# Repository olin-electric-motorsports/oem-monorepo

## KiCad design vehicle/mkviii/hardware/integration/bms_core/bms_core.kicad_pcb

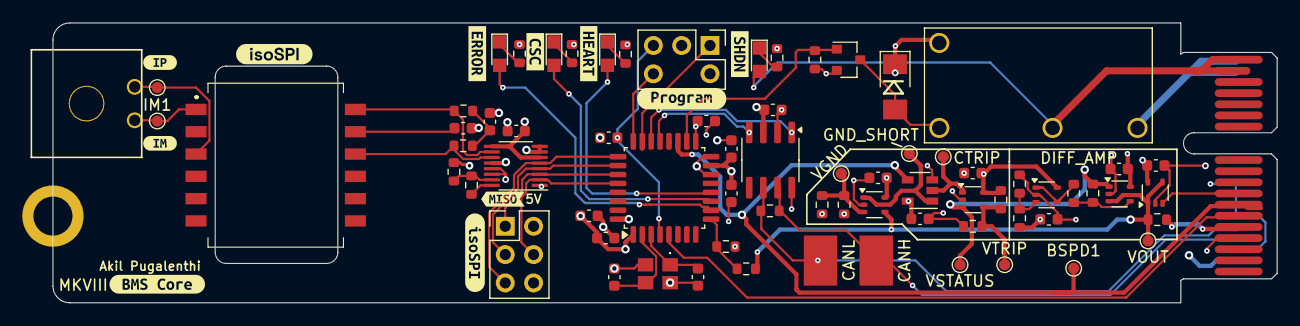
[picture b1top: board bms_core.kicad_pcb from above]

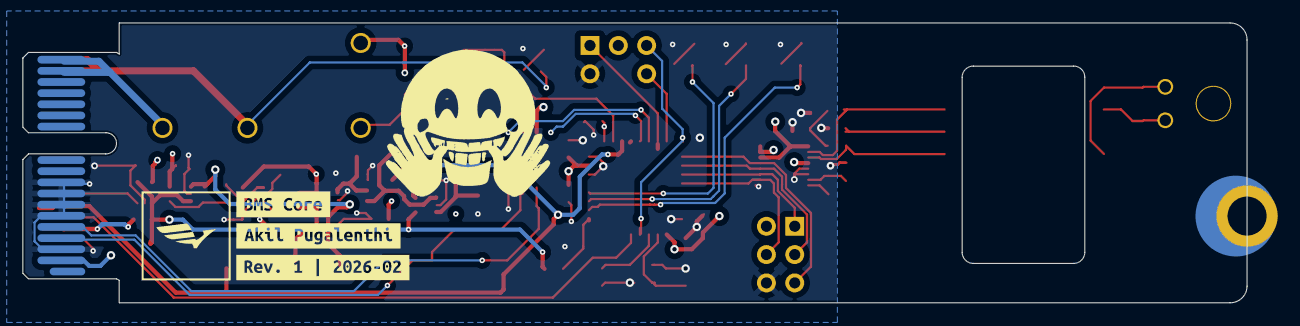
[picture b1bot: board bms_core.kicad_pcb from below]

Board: 4 copper layers, 109.8 x 25.1 mm, 87 parts (3 on the bottom side), 48 nets.

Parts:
BSPD1: BSPD_CURRENT_THRESH; TestPoint_Pad_D1.0mm
C1, C16, C17, C21, C22: C_0.1uF_16V; C_0603_1608Metric
C6, C9, C10, C11, C12, C13: C_0.1uF; C_0603
C7, C8: C_10nF; C_0603
C14, C15: C_30pF_50V; C_0603_1608Metric
C18: C_4.7uF_25V; C_0603_1608Metric
C19: C_10nF_50V; C_0603_1608Metric
C20: C_1uF_25V; C_0603_1608Metric
CANH: CANH1; TP_Hook_SMD
CANL: CANL1; TP_Hook_SMD
D1: LED_AMBER; CHIPLED_0805
D2: LED_GREEN; CHIPLED_0805
D3: LED_RED; CHIPLED_0805
D5: D_Zener_18V_SMBJ5355B-TP; DO-214AA
D6: LED_BLUE; CHIPLED_0805
GND_SHORT: GND_SHORT; TestPoint_Pad_D1.0mm
H2: CONN_MountingHole; PCIe_Mount
IM1: TP_1mm; TestPoint_Pad_D1.0mm
IP1: TP_1mm; TestPoint_Pad_D1.0mm
J1: isoSPI Header; PinHeader_2x03_P2.54mm_Vertical
J3: MicroFit_RA_2
J4: J_Programming_Pin_Header; J_Programming_Pin_Header_Keyed
J5: J_PCIe_x1; J_PCIe_x1_Key
K1: Relay_G5Q-1A4-DC5; Relay_SPST_OMRON-G5Q-1A4_OEM
Q1: SSM3K333R; SOT-23F
R1, R3, R21, R23: 1KR; R_0603
R2: R_5.1k; R_0603_1608Metric
R4: R_10k; R_0603_1608Metric
R5: R_120; R_0603_1608Metric
R7, R12, R15, R16, R19, R24, R25: R_10K; R_0603
R8, R9, R18: R_1K; R_0603
R10, R11: R_60.4; R_0603
R17: R_1M; R_0603
R20: R_576; R_0603
T1: HM2112ZNLT
TP4: CURRENT_TRIP; TestPoint_Pad_D1.0mm
U1, U4, U5, U6, U8: MCP6001; SOT-353_SC-70-5
U3: LTC6820HMS; MSOP-16_3x4mm_P0.5mm
U7: SN74LVC1G32DBVR; SOT-23-5_OEM
U10: STM32G441KBT6; LQFP-32_7x7mm_P0.8mm
U11: MCP2561-E_SN; SOIC-8_3.9x4.9mm_P1.27mm
VGND: V_GND_THRESHOLD; TestPoint_Pad_D1.0mm
VOUT: VOUT; TestPoint_Pad_D1.0mm
VSTATUS: VSTATUS; TestPoint_Pad_D1.0mm
VTRIP: VTRIP; TestPoint_Pad_D1.0mm
Y3: X_16MHz_18pF; FA238160000MBC0 (X_16MHz_18pF_SMD - FA-238_16.0000MB-C0)
kibuzzard-63B930AD: G***; kibuzzard-63B930AD
kibuzzard-63B9305B: G***; kibuzzard-63B9305B
kibuzzard-63B93076: G***; kibuzzard-63B93076
kibuzzard-63BB8A3F: G***; kibuzzard-63BB8A3F
kibuzzard-63BB8A53: G***; kibuzzard-63BB8A53
kibuzzard-63BF4A21: G***; kibuzzard-63BF4A21
kibuzzard-63BF57C4: G***; kibuzzard-63BF57C4
kibuzzard-673AE5D1: G***; kibuzzard-673AE5D1
kibuzzard-673AE69E: G***; kibuzzard-673AE69E
kibuzzard-673AE677: G***; kibuzzard-673AE677
kibuzzard-673AE688: G***; kibuzzard-673AE688
kibuzzard-698026CF: G***; kibuzzard-698026CF
kibuzzard-69802617: G***; kibuzzard-69802617
kibuzzard-69802858: G***; kibuzzard-69802858

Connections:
+3V3: C16.1, C17.1, C18.1, C19.1, C20.1, J4.3, J5.A2 (3.3V), U10.1 (VDD), U10.15 (VDDA), U10.17 (VDD)
+5V: C1.2, C6.1, C9.1, C10.1, C11.1, C12.1, C13.1, C22.1, D5.1 (K), J1.2, J5.B5 (5V), K1.5, R12.2, R17.1, R19.2, R24.1, U1.5 (V+), U3.6 (VDDS), U3.7 (POL), U3.8 (PHA), U3.9 (VDD), U3.12 (MSTR), U4.5 (V+), U5.5 (V+), U6.5 (V+), U7.5 (VCC), U8.5 (V+), U11.3 (VDD)
/BMS_RELAY_DRIVE: Q1.1 (G), R7.2, U10.18 ((TIM4_ETR/USART1_CK/GPIO_EXTI8)PA8)
/BSPD Current Sensor Trigger/CURRENT_TRIP: TP4.1, U6.1, U7.2 (in)
/BSPD Current Sensor Trigger/GND_SHORT: GND_SHORT.1, U5.1, U7.1 (in)
/BSPD Current Sensor Trigger/VSTATUS: R15.2, U4.1, U6.3 (+), VSTATUS.1
/BSPD Current Sensor Trigger/VTRIP: R19.1, R20.1, U6.4 (-), VTRIP.1
/BSPD Current Sensor Trigger/V_GND_THRESHOLD: R17.2, R18.1, U5.3 (+), VGND.1
/BSPD_CURRENT_THRESH: BSPD1.1, J5.B7 (io_3), U7.4 (out), U10.19 ((TIM2_CH3/TIM15_BKIN/USART1_TX/GPIO_EXT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)
/CANH: CANH.1, J5.A4 (CAN+), R5.1, U11.7 (CANH)
/CANL: CANL.1, J5.A5 (CAN-), R5.2, U11.6 (CANL)
/CAN_RX: U10.21 ((FDCAN1_RX/GPIO_EXTI11)PA11), U11.4 (RXD)
/CAN_TX: U10.22 ((FDCAN1_TX/GPIO_EXTI12)PA12), U11.1 (TXD)
/CSC_Comms: D2.2 (A), U10.11 ((TIM3_CH1/TIM16_CH1/GPIO_EXTI6/ADC2_IN3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)
/Error: D3.2 (A), U10.10 ((TIM2_ETR/TIM2_CH1/GPIO_EXTI5/ADC2_IN13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)
/FAN_PWM: J5.B6 (io_1), U10.5 ((TIM2_ETR/TIM2_CH1/GPIO_EXTI0/ADC2_IN1/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)
/Heartbeat: D1.2 (A), U10.12 ((TIM3_CH2/TIM17_CH1/GPIO_EXTI7/ADC2_IN4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)
/IM: IM1.1, J3.1, T1.1
/IP: IP1.1, J3.2, T1.3
/ISO_CS: J1.5, U3.5 (~CS), U10.25 ((TIM2_ETR/TIM2_CH1/GPIO_EXTI15)PA15)
/ISO_MISO: J1.1, U3.3 (MISO), U10.27 ((TIM17_BKIN/SPI1_MISO/TIM3_CH1/TIM16_CH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)
/ISO_MOSI: J1.4, U3.2 (MOSI), U10.28 ((TIM17_CH1/SPI1_MOSI/TIM3_CH2/TIM16_BKI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)
/ISO_SCK: J1.3, U3.4 (SCK), U10.26 ((TIM3_ETR/SPI1_SCK/TIM4_ETR/TIM2_CH2/GP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)
/NRST: C21.1, J4.4, U10.4 ((GPIO_EXTI10)PG10-NRST)
/SHDN_IN: J5.A17 (SHDN_IN/io_22), J5.A18 (SHDN_IN/io_24), K1.3
/SHDN_OUT: D6.2 (A), J5.B17 (SHDN_OUT/io_23), J5.B18 (SHDN_OUT/io_25), K1.2
/SWCLK: J4.5, U10.24 ((SYS_JTCK-SWCLK/GPIO_EXTI14)PA14)
/SWDIO: J4.1, U10.23 ((SYS_JTMS-SWDIO/GPIO_EXTI13)PA13)
/VOUT_CURRENT_SENSE: R2.1, R12.1, U1.1, U1.4 (-), U4.3 (+), U5.4 (-), VOUT.1
GND: C1.1, C6.2, C7.2, C8.2, C9.2, C10.2, C11.2, C12.2, C13.2, C14.2, C15.2, C16.2, C17.2, C18.2, C19.2, C20.2, C21.2, C22.2, J1.6, J4.2, J5.A3 (GND), J5.A6 (io_0), J5.A7 (io_2), J5.A8 (io_4), J5.A9 (io_6), J5.B4 (GND), Q1.2 (S), R1.2, R3.2, R4.2, R7.1, R9.2, R18.2, R20.2, R21.2, R23.2, R25.2, U1.2 (V-), U3.1 (EN), U3.13 (SLOW), U3.14 (GND), U4.2 (V-), U5.2 (V-), U6.2 (V-), U7.3 (GND), U8.2 (V-), U10.14 (VSSA), U10.16 (VSS), U10.32 (VSS), U11.2 (VSS), U11.8 (STBY), Y3.2, Y3.4
unnamed: C7.1, R10.2, R11.1
unnamed: C8.1, T1.11
unnamed: D1.1 (K), R1.1
unnamed: D2.1 (K), R3.1
unnamed: D3.1 (K), R21.1
unnamed: D5.2 (A), K1.1, Q1.3 (D)
unnamed: D6.1 (K), R23.1
unnamed: J5.B8 (io_5), U1.3 (+)
unnamed: R8.1, U3.16 (IBIAS)
unnamed: R8.2, R9.1, U3.15 (ICMP)
unnamed: R10.1, T1.12, U3.10 (IM)
unnamed: R11.2, T1.10, U3.11 (IP)
unnamed: R15.1, R16.2, U4.4 (-)
unnamed: R24.2, R25.1, U8.3 (+)
unnamed: R16.1, U8.1, U8.4 (-)
unnamed: R2.2, R4.1, U10.9 ((USART2_CK/TIM3_CH2/GPIO_EXTI4/ADC2_IN1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)
unnamed: C15.1, U10.2 (PF0-OSC_IN), Y3.3
unnamed: C14.1, U10.3 (PF1-OSC_OUT), Y3.1

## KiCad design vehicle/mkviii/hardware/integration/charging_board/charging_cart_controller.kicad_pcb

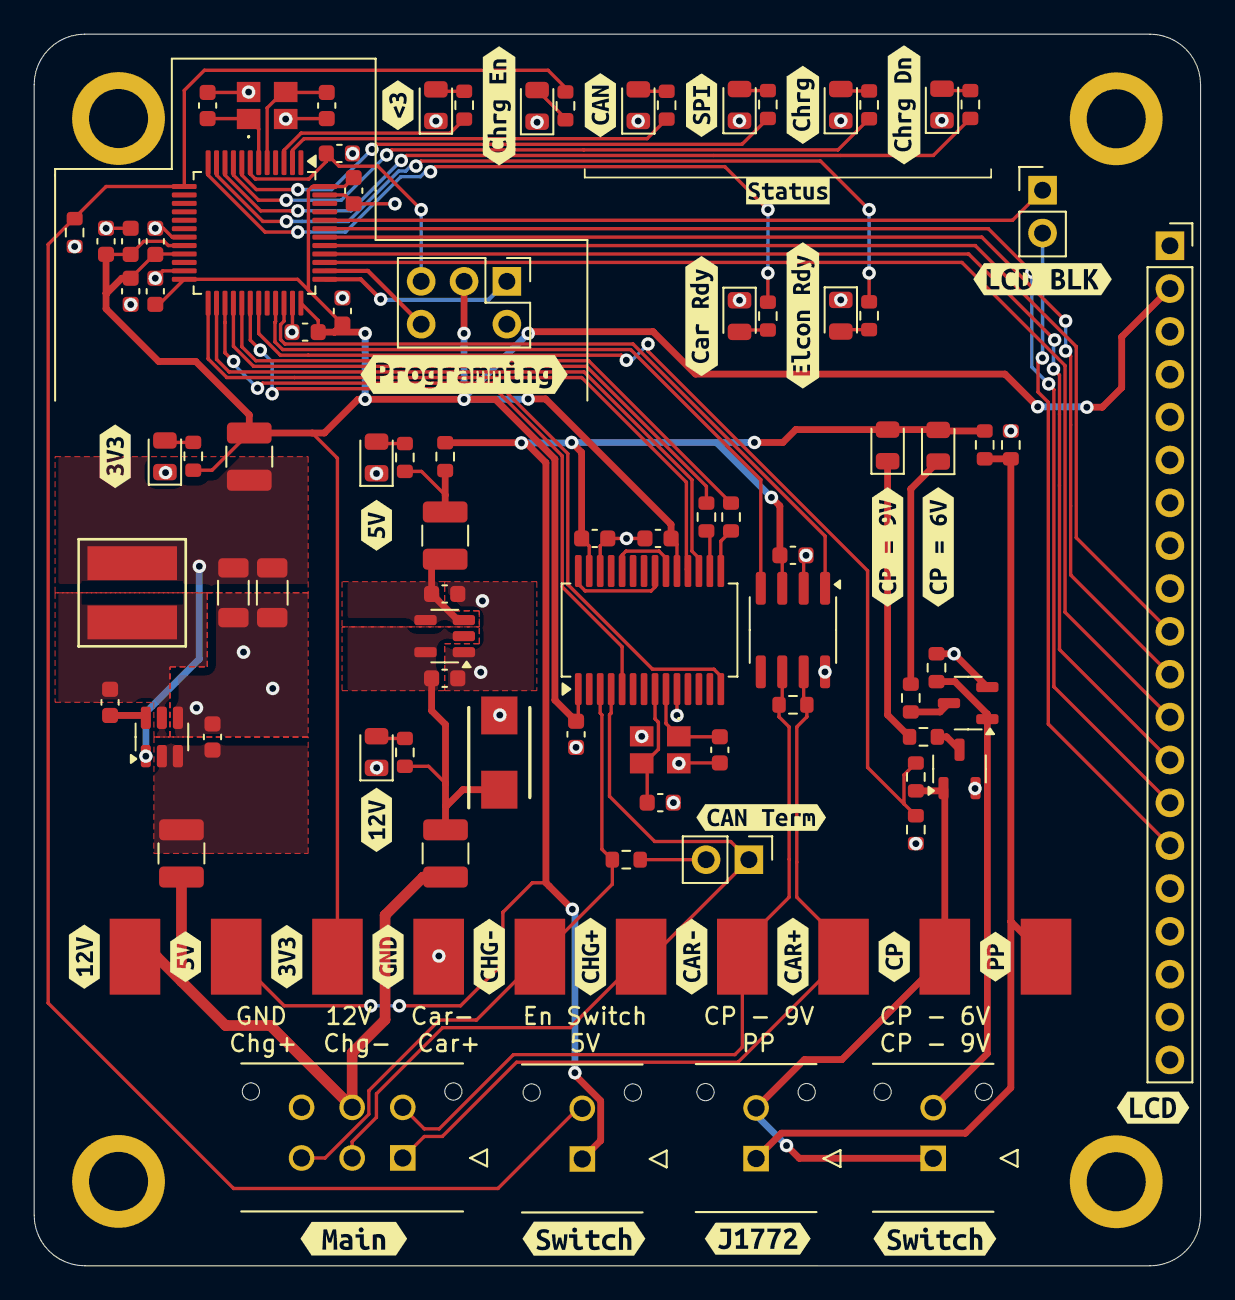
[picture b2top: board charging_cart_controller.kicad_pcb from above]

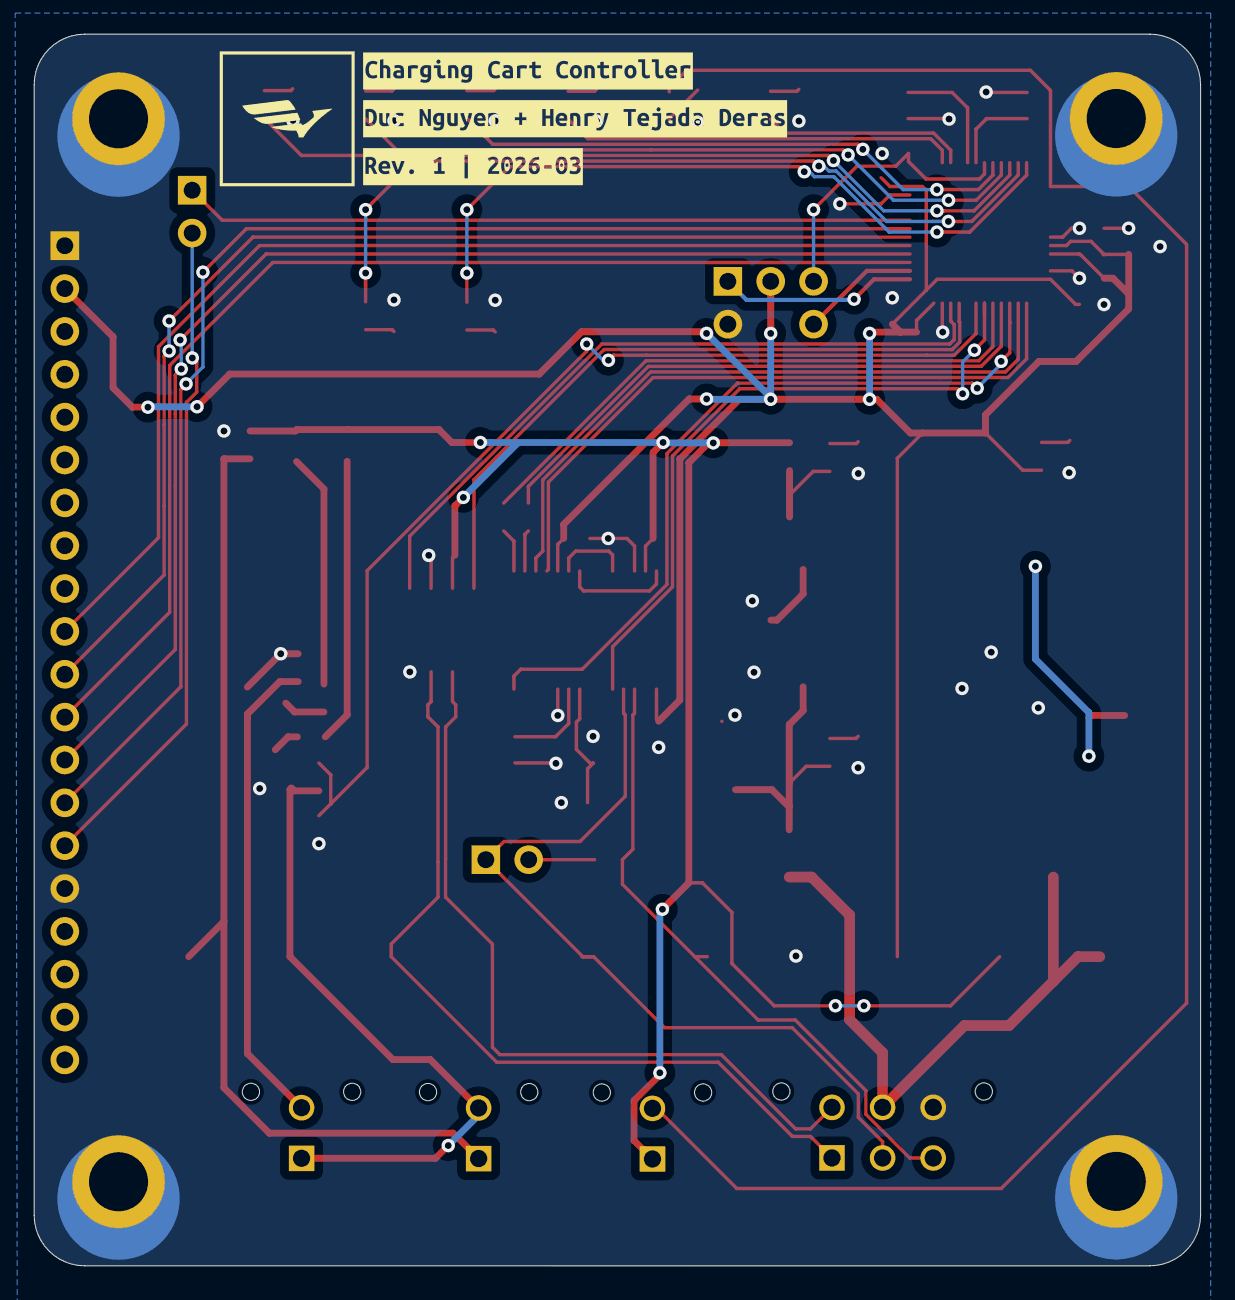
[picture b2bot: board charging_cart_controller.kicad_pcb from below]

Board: 2 copper layers, 69.1 x 73.0 mm, 132 parts (3 on the bottom side), 69 nets.

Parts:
C1, C4, C5, C13, C15, C16, C17, C21: C_0.1uF; C_0603_1608Metric
C2, C3, C14: C_1uF; C_0603_1608Metric
C6: C_10nF; C_0603_1608Metric
C7, C8: C_30pF_50V; C_0603_1608Metric
C9: C_10uF_10V; C_0603_1608Metric
C10, C23: C_0.1uF_50V; C_0603_1608Metric
C11, C12: C_22uF_25V; C_1206_3216Metric
C18: C_4.7uF; C_0603_1608Metric
C19, C20: C_30pF; C_0603_1608Metric
C22: C_1uF_50V; C_0603_1608Metric
D1, D2: WHITE; D_0805_2012Metric
D3: on/off; D_0805_2012Metric
D4: Charging Status; D_0805_2012Metric
D5: CAN Status; D_0805_2012Metric
D6, D7, D8, D9, D10, D11: LED; D_0805_2012Metric
D15: D_Zener_18V_5W; D_Zener_18V_5W_DO214AA - DIOM5336X262N
D16: Fully Charged Status; D_0805_2012Metric
D17: SPI Status; D_0805_2012Metric
F1, F2, F3, F4: F_500mA_16V; Fuse_1210_3225Metric
H1, H2, H3, H4: H_MountingHole
J2: Conn_01x20_Socket; PinSocket_1x20_P2.54mm_Vertical
J4: CONN_01x02; PinHeader_1x02_P2.54mm_Vertical
J5, J9, J10: J_Molex_Header_01x02_VT; J_Molex_Header_01x02_VT - 43045-02YY_121314
J6: Conn_01x02_Pin; PinHeader_1x02_P2.54mm_Vertical
J7: J_Programming_Pin_Header; J_Programming_Pin_Header_Keyed
J8: J_Molex_Header_02x03_VT; J_Molex_Header_02x03_VT - 43045-06YY_121314
L1: L_3.9uH_2A; IND_BOURNS_SRR5018 (L_3.9uH_2A_55m_SMD)
Q2, Q3: SSM3K333R,LF; SOT-23-3
R1, R14: R_120; R_0603_1608Metric
R2, R3, R8, R15, R16, R17, R19, R20, R21, R22, R23, R24, R25: R_1k; R_0603_1608Metric
R4, R9, R10: R_330; R_0603_1608Metric
R5: R_2.2k; R_0603_1608Metric
R6: R_1.91k; R_0603_1608Metric
R7: R_1.43k; R_0603_1608Metric
R11: R_0; R_0603_1608Metric
R12, R13: R_500; R_0603_1608Metric
TP1, TP3, TP5, TP6, TP8, TP9: TP_SMD; TP_Hook_SMD
TP2, TP4, TP11: TP; TP_Hook_SMD
TP10: Test_Point_SMD; TP_Hook_SMD
U1: TLV70450DBVR; SOT-23-5
U2: AP63203WU-7; SOT-23-6
U4: MCP25625-E/SS; SSOP-28_5.3x10.2mm_P0.65mm
U6: STM32G441CBT6; LQFP-48_7x7mm_P0.5mm
U9: MCP2561-E_SN; SOIC-8_3.9x4.9mm_P1.27mm
Y1, Y3: X_16MHz_18pF; FA238160000MBC0 (X_16MHz_18pF_SMD - FA-238_16.0000MB-C0)
kibuzzard-69B5A4A4: G***; kibuzzard-69B5A4A4
kibuzzard-69B5A49D: G***; kibuzzard-69B5A49D
kibuzzard-69B5A184: G***; kibuzzard-69B5A184
kibuzzard-69B5A189: G***; kibuzzard-69B5A189
kibuzzard-69B6B8E8: G***; kibuzzard-69B6B8E8
kibuzzard-69B6B8EC: G***; kibuzzard-69B6B8EC
kibuzzard-69B6B9E1: G***; kibuzzard-69B6B9E1
kibuzzard-69B6B40C: G***; kibuzzard-69B6B40C
kibuzzard-69B6BA0D: G***; kibuzzard-69B6BA0D
kibuzzard-69B6BA6C: G***; kibuzzard-69B6BA6C
kibuzzard-69B6BA12: G***; kibuzzard-69B6BA12
kibuzzard-69B6BC07: G***; kibuzzard-69B6BC07
kibuzzard-69B6BF6C: G***; kibuzzard-69B6BF6C
kibuzzard-69B6BF72: G***; kibuzzard-69B6BF72
kibuzzard-69B6C89F: G***; kibuzzard-69B6C89F
kibuzzard-69B6C98F: G***; kibuzzard-69B6C98F
kibuzzard-69B6CA04: G***; kibuzzard-69B6CA04
kibuzzard-69B85D85: G***; kibuzzard-69B85D85
kibuzzard-69B545AB, kibuzzard-69B545AB#2: G***; kibuzzard-69B545AB
kibuzzard-69B545D0, kibuzzard-69B545D0#2: G***; kibuzzard-69B545D0
kibuzzard-69B545E8, kibuzzard-69B545E8#2: G***; kibuzzard-69B545E8
kibuzzard-69B626F3: G***; kibuzzard-69B626F3
kibuzzard-69B856EE: G***; kibuzzard-69B856EE
kibuzzard-69B858C4: G***; kibuzzard-69B858C4
kibuzzard-69B861A4: G***; kibuzzard-69B861A4
kibuzzard-69B6277C: G***; kibuzzard-69B6277C
kibuzzard-69B62712: G***; kibuzzard-69B62712
kibuzzard-69B62739: G***; kibuzzard-69B62739
kibuzzard-69B62752: G***; kibuzzard-69B62752
kibuzzard-69B62762: G***; kibuzzard-69B62762
kibuzzard-69B62772: G***; kibuzzard-69B62772
kibuzzard-69B85855: G***; kibuzzard-69B85855

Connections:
+3.3V: C1.1, C4.1, C6.1, C13.1, C14.1, C15.1, C16.1, C18.1, C22.1, C23.1, F1.2, J2.2, J7.3, R15.1, TP1.1, U4.1 (VIO), U4.19 (VDD), U6.20 (VREF+), U6.21 (VDDA), U6.24 (VDD), U6.36 (VDD), U6.48 (VDD)
+5V: C5.2, C21.1, D1.2 (A), D2.2 (A), J5.1, R4.1, R11.1, TP4.1, U4.27 (VDDA), U9.3 (VDD)
+12V: F2.1, F3.1, J8.5, TP11.1
/12 -> 5 V Converter Input: C2.1, D15.1 (K), F3.2, R2.1, U1.2 (IN), U1.5 (NC_2)
/12 -> 5 V Converter Output: C3.1, F4.1, U1.3 (OUT), U1.4 (NC_1)
/CAN_CTRLR_SPI_MISO: R12.1, U6.28 ((EVENTOUT/COMP4_OUT/USART3_RTS/USART3_D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)
/CAN_CTRLR_SPI_MOSI: R13.1, U6.29 ((EVENTOUT/SPI2_MOSI/I2S2_SD/TIM1_CH3N/C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)
/CAN_CTRLR_SPI_SCK: U4.14 (SCK), U6.27 ((EVENTOUT/LPUART1_CTS/USART3_NSS/USART3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)
/CAN_RX: U6.33 ((EVENTOUT/TIM1_BKIN2/TIM1_CH4/TIM4_CH1/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), U9.4 (RXD)
/CAN_Status: R17.1, U6.2 ((EVENTOUT/TIM8_CH4N/TIM1_CH1N/TIM1_BKIN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)
/CAN_TX: U6.34 ((EVENTOUT/TIM1_ETR/TIM4_CH2/FDCAN1_TX/C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), U9.1 (TXD)
/CAR_CAN_+: J8.1, R1.1, TP3.1, U9.7 (CANH)
/CAR_CAN_-: J8.4, R1.2, TP9.1, U9.6 (CANL)
/CHARGER_CAN_+: J4.1, J8.2, TP6.1, U4.4 (CANH)
/CHARGER_CAN_-: J8.3, R14.2, TP8.1, U4.3 (CANL)
/CHARGER_STBY: U4.5 (STBY), U6.30 ((EVENTOUT/SAI1_SCK_A/SAI1_CK2/TIM4_ETR/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)
/Car_Ready: R22.2, U6.12 ((EVENTOUT/SAI1_FS_B/USART2_CK/SPI3_NSS/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)
/Charging_ON/OFF_Status: J5.2, R20.1, R24.1, U6.13 ((EVENTOUT/UCPD1_FRSTX2/UCPD1_FRSTX1/SPI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)
/Charging_Status: R23.1, U6.9 ((EVENTOUT/TIM15_CH1N/USART2_DE/USART2_R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)
/EVSE PWM: R6.2, R8.1, U6.31 ((EVENTOUT/SAI1_FS_A/TIM2_CH3/TIM15_BKIN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)
/Elcon_Ready: R25.2, U6.11 ((EVENTOUT/SAI1_MCLK_A/LPUART1_RX/TIM15_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)
/Fully_Charged_Status: R3.1, U6.10 ((EVENTOUT/UCPD1_FRSTX2/UCPD1_FRSTX1/LPU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)
/Heartbeat: R16.2, U6.3 ((EVENTOUT/GPIO_EXTI14)PC14-OSC32_IN)
/LCD_BLK: J6.1, U6.44 ((EVENTOUT/LPTIM1_IN2/TIM3_CH4/COMP3_OUT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)
/LCD_SPI_MISO: J2.10, U6.41 ((EVENTOUT/SAI1_MCLK_B/TIM17_BKIN/USART2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)
/LCD_SPI_MOSI: J2.11, U6.42 ((EVENTOUT/SAI1_SD_B/LPTIM1_IN1/TIM17_CH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)
/LCD_SPI_SCK: J2.13, U6.40 ((EVENTOUT/SAI1_SCK_B/TIM3_ETR/USART2_TX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)
/NRST: C17.1, J7.4, U6.7 ((EVENTOUT/RCC_MCO/GPIO_EXTI10)PG10-NRST)
/SPI_Status: R21.1, U6.8 ((EVENTOUT/TIM2_ETR/TIM8_ETR/TIM8_BKIN/C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)
/SWCLK: J7.5, U6.38 ((EVENTOUT/SAI1_FS_B/USART2_TX/TIM1_BKIN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)
/SWDIO: J7.1, U6.37 ((EVENTOUT/SAI1_SD_B/TIM4_CH3/USART3_NSS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)
/control_pilot: J9.2, J10.1, Q3.1 (G), R6.1, TP5.1
/proximity_pilot: J9.1, R4.2, R5.1, TP2.1
/~CAN_CTRLR_RST: U4.18 (~RESET), U6.25 ((EVENTOUT/LPUART1_TX/USART3_RX/TIM2_CH4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)
/~CAN_CTRLR_SPI_CS: U4.17 (~CS), U6.26 ((EVENTOUT/LPUART1_RTS/LPUART1_DE/USART3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)
/~LCD_RST: J2.14, U6.43 ((EVENTOUT/SAI1_FS_B/LPTIM1_ETR/TIM8_BKI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)
/~LCD_SPI_CS: J2.12, U6.39 ((EVENTOUT/TIM2_ETR/TIM1_BKIN/USART2_RX/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)
GND: C1.2, C2.2, C3.2, C4.2, C5.1, C6.2, C7.2, C8.2, C9.2, C11.2, C12.2, C13.2, C14.2, C15.2, C16.2, C17.2, C18.2, C19.2, C20.2, C21.2, C22.2, C23.2, D3.1 (K), D4.1 (K), D5.1 (K), D6.1 (K), D7.1 (K), D8.1 (K), D9.1 (K), D10.1 (K), D11.1 (K), D15.2 (A), D16.1 (K), D17.1 (K), H1.1, H2.1, H3.1, H4.1, J2.1, J2.16, J7.2, J8.6, Q2.2 (S), Q3.2 (S), R5.2, R7.2, R8.2, R24.2, TP10.1, U1.1 (GND), U2.4 (GND), U4.10 (GND), U4.26 (VSS), U6.19 (VSSA), U6.23 (VSS), U6.35 (VSS), U6.47 (VSS), U9.2 (VSS), U9.8 (STBY), Y1.2, Y1.4, Y3.2, Y3.4
unnamed: D1.1 (K), R9.1
unnamed: D2.1 (K), R10.1
unnamed: D3.2 (A), R20.2
unnamed: D4.2 (A), R23.2
unnamed: D5.2 (A), R17.2
unnamed: D6.2 (A), R2.2
unnamed: D7.2 (A), R19.2
unnamed: D8.2 (A), R22.1
unnamed: D9.2 (A), R25.1
unnamed: D10.2 (A), R15.2
unnamed: D11.2 (A), R16.1
unnamed: D16.2 (A), R3.2
unnamed: D17.2 (A), R21.2
unnamed: F4.2, R11.2, R19.1
unnamed: J2.15, J6.2
unnamed: J4.2, R14.1
unnamed: Q2.3 (D), R10.2
unnamed: J10.2, Q2.1 (G), R7.1
unnamed: Q3.3 (D), R9.2
unnamed: C10.1, U2.6 (BST)
unnamed: C9.1, F2.2, U2.2 (EN), U2.3 (VIN)
unnamed: C11.1, C12.1, F1.1, L1.2, U2.1 (FB)
unnamed: C10.2, L1.1, U2.5 (SW)
unnamed: C8.1, U4.9 (OSC1), Y1.1
unnamed: C7.1, U4.8 (OSC2), Y1.3
unnamed: U4.21 (RxCAN), U4.28 (RXD)
unnamed: R13.2, U4.15 (SI)
unnamed: R12.2, U4.16 (SO)
unnamed: U4.20 (TxCAN), U4.24 (TXD)
unnamed: C19.1, U6.6 ((EVENTOUT/SPI2_SCK/I2S2_CK/GPIO_EXTI1)P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), Y3.1
unnamed: C20.1, U6.5 ((EVENTOUT/TIM1_CH3N/SPI2_NSS/I2S2_WS/I2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), Y3.3

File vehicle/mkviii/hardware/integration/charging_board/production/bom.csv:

Designator,Footprint,Quantity,Value,LCSC Part #
"C1, C13, C15, C16, C17, C21, C4, C5",0603,8,C_0.1uF,CL10B104KB8NNWC
"C10, C23",0603,2,C_0.1uF_50V,CL10B104KB8NNWC
"C11, C12",1206,2,C_22uF_25V,CL31A226KAHNNNE
"C14, C2",0603,2,C_1uF,UMK107BJ105KA-T
C18,0603,1,C_4.7uF,GRT188R61E475ME13D
"C19, C20",0603,2,C_30pF,CML0603C0G300JT50V
C22,0603,1,C_1uF_50V,UMK107BJ105KA-T
C3,0603,1,C_1uF,CL10B105KA8NNNC
C6,0603,1,C_10nF,CL10B103KB8NNNC
"C7, C8",0603,2,C_30pF_50V,CML0603C0G300JT50V
C9,0603,1,C_10uF_10V,GRM188D71A106KA73D
"D1, D2",0805,2,WHITE,QBLP631-IW
"D10, D11, D6, D7, D8, D9",0805,6,LED,QBLP631-IW
D15,D_Zener_18V_5W_DO214AA - DIOM5336X262N,1,D_Zener_18V_5W,SMBJ5355B-TP
D16,0805,1,Fully Charged Status,LTST-C170KGKT
D17,0805,1,SPI Status,QBLP631-IW
D3,0805,1,on/off,LTST-C171KRKT
D4,0805,1,Charging Status, LTST-C171AKT 
D5,0805,1,CAN Status,LTST-C171TBKT
"F1, F2, F3, F4",1210,4,F_500mA_16V,0ZCH0050FF2G
"J10, J5, J9",J_Molex_Header_01x02_VT - 43045-02YY_121314,3,J_Molex_Header_01x02_VT,43045-0212
J2,PinSocket_1x20_P2.54mm_Vertical,1,Conn_01x20_Socket,
J4,PinHeader_1x02_P2.54mm_Vertical,1,CONN_01x02,732-5315-ND
J6,PinHeader_1x02_P2.54mm_Vertical,1,Conn_01x02_Pin,
J7,J_Programming_Pin_Header_Keyed,1,J_Programming_Pin_Header,
J8,J_Molex_Header_02x03_VT - 43045-06YY_121314,1,J_Molex_Header_02x03_VT,43045-0614
L1,IND_BOURNS_SRR5018 (L_3.9uH_2A_55m_SMD),1,L_3.9uH_2A,SRR5018-3R9Y
"Q2, Q3",SOT-23-3,2,"SSM3K333R,LF",
R1,0603,1,R_120,RC0603FR-13120RL
"R10, R4, R9",0603,3,R_330,RMCF0603FT330R (or WR06X3300FTL)
R11,0603,1,R_0,RMCF0603ZT0R00
"R12, R13",0603,2,R_500,541-3305-1-ND
R14,0603,1,R_120,667-ERJ-6ENF1200V
"R15, R16, R17, R19, R2, R20, R21, R22, R23, R24, R25, R3, R8",0603,13,R_1k,RMCF0603FT1K00 (or ERJ-3GEYJ102V)
R5,0603,1,R_2.2k,WR06X222 JTL
R6,0603,1,R_1.91k,RMCF0603FT1K91
R7,0603,1,R_1.43k,RMCF0603FT1K43
"TP1, TP3, TP5, TP6, TP8, TP9",TP_Hook_SMD,6,TP_SMD,5019
TP10,TP_Hook_SMD,1,Test_Point_SMD,5019
"TP11, TP2, TP4",TP_Hook_SMD,3,TP,5019
U1,SOT-23-5,1,TLV70450DBVR,TLV70450DBVR
U2,SOT-23-6,1,AP63203WU-7,AP63203WU-7
U4,SSOP-28_5.3x10.2mm_P0.65mm,1,MCP25625-E/SS,MCP25625-E/SS-ND
U6,LQFP-48_7x7mm_P0.5mm,1,STM32G441CBT6,STM32G441CBT6
U9,SOIC-8_3.9x4.9mm_P1.27mm,1,MCP2561-E_SN,MCP2561-E/SN
"Y1, Y3",FA238160000MBC0 (X_16MHz_18pF_SMD - FA-238_16.0000MB-C0),2,X_16MHz_18pF,FA-238 16.0000MB-C0

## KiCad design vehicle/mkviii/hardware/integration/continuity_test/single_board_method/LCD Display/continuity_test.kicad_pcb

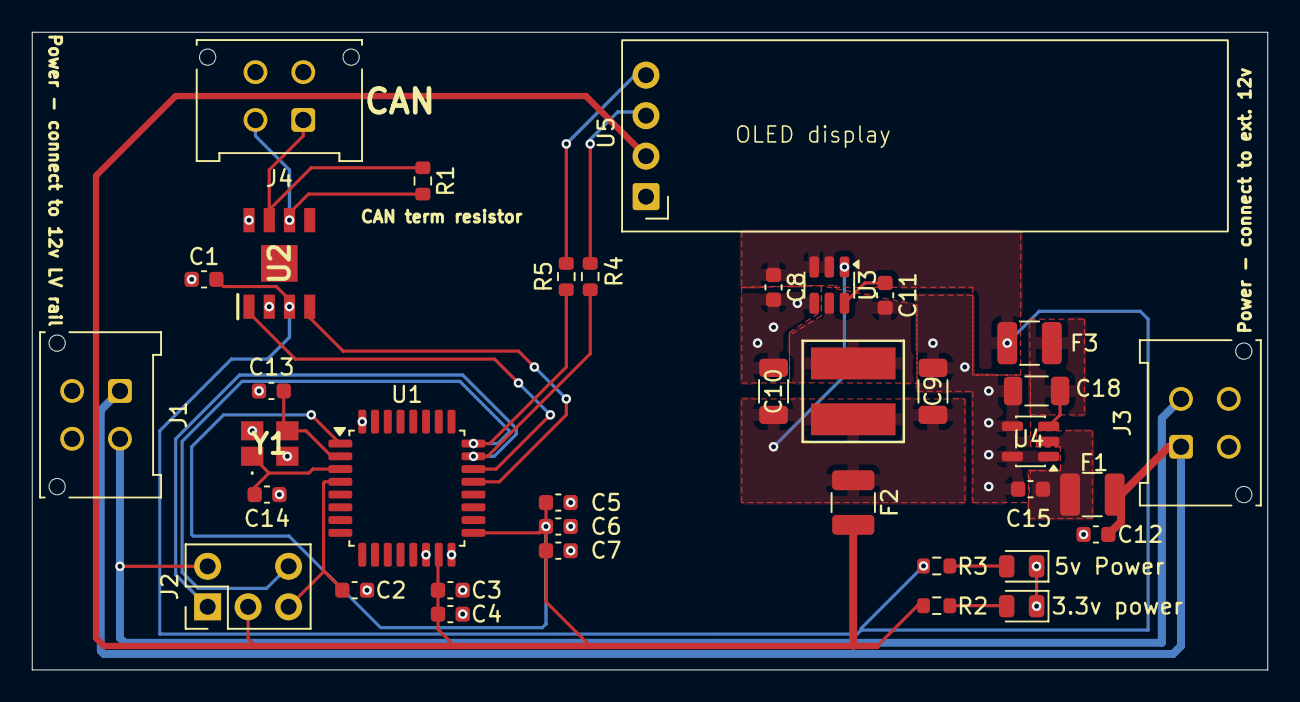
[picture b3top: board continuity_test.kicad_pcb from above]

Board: 2 copper layers, 77.5 x 40.0 mm, 37 parts (0 on the bottom side), 21 nets.

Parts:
3.3v power: 3V3 POWER; D_0805_2012Metric
5v Power: 5V POWER; D_0805_2012Metric
C1, C2, C5, C6, C11: C_0.1uF; C_0603_1608Metric
C3: C_10nF; C_0603_1608Metric
C4, C15: C_1uF; C_0603_1608Metric
C7: C_4.7uF; C_0603_1608Metric
C8, C12: C_10uF; C_0603_1608Metric
C9, C10: C_22uF; C_1206_3216Metric
C13, C14: C_30pF; C_0603_1608Metric
C18: C_1uF; C_1206_3216Metric
F1, F2, F3: F_500mA_16V; Fuse_1210_3225Metric
J1, J3, J4: Conn_01x02_Pin; Molex_Micro-Fit_3.0_43045-0412_2x02_P3.00mm_Vertical
J2: Programming_Pin_Header; J_Programming_Pin_Header_Keyed
L1: L_3.9uH; IND_BOURNS_SRR5018 (L_3.9uH_2A_55m_SMD)
R1: R_120; R_0603_1608Metric
R2, R3: R_1K; R_0603_1608Metric
R4, R5: R_2.2k_0.1W; R_0603_1608Metric
U1: STM32G441KBT6; LQFP-32_7x7mm_P0.8mm
U2: MCP2561-E_SN; U_1.222V-Buck-Conv_RT6285GSP_ SOP-8
U3: AP63203WU-7; SOT-23-6
U4: TLV70450DBVR; SOT-23-5
U5: ER_OLEDM0.91_1x-I2C
Y1: X_Crystal_16MHz_18pF; FA238160000MBC0 (X_16MHz_18pF_SMD - FA-238_16.0000MB-C0)

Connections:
+3V3: C3.1, C4.1, C5.1, C6.1, C7.1, F2.2, J2.3, R2.1, U1.1 (VDD), U1.15 (VDDA), U1.17 (VDD), U5.2 (VCC)
+5V: C1.2, C8.1, F3.2, R3.1, U2.3 (VDD), U3.2 (EN), U3.3 (VIN)
+12V: C12.1, C15.1, F1.1, F1.2, J1.1, J3.1, U4.2 (IN)
/CAN_+: J4.1, R1.1, U2.7 (CANH)
/CAN_-: J4.2, R1.2, U2.6 (CANL)
/CAN_RX: U1.21 ((FDCAN1_RX/GPIO_EXTI11)PA11), U2.4 (RXD)
/CAN_TX: U1.22 ((FDCAN1_TX/GPIO_EXTI12)PA12), U2.1 (TXD)
/I2C_SCL: J2.1, R4.1, U1.23 ((SYS_JTMS-SWDIO/GPIO_EXTI13)PA13)
/I2C_SDA: J2.5, R5.1, U1.24 ((SYS_JTCK-SWCLK/GPIO_EXTI14)PA14)
/NRST: C2.1, J2.4, U1.4 ((GPIO_EXTI10)PG10-NRST)
GND: 3.3v power.1 (K), 5v Power.1 (K), C1.1, C2.2, C3.2, C4.2, C5.2, C6.2, C7.2, C8.2, C9.2, C10.2, C12.2, C13.2, C14.2, C15.2, C18.2, J1.2, J2.2, J3.2, U1.14 (VSSA), U1.16 (VSS), U1.32 (VSS), U2.2 (VSS), U2.8 (STBY), U3.4 (GND), U4.1 (GND), U4.4 (NC_1), U4.5 (NC_2), U5.1 (GND), Y1.2, Y1.4
unnamed: 3.3v power.2 (A), R2.2
unnamed: 5v Power.2 (A), R3.2
unnamed: C13.1, U1.2 (PF0-OSC_IN), Y1.3
unnamed: C14.1, U1.3 (PF1-OSC_OUT), Y1.1
unnamed: C11.1, U3.6 (BST)
unnamed: C9.1, C10.1, F2.1, L1.2, U3.1 (FB)
unnamed: C11.2, L1.1, U3.5 (SW)
unnamed: C18.1, F3.1, U4.3 (OUT)
unnamed: R4.2, U5.3 (SCL)
unnamed: R5.2, U5.4 (SDA)

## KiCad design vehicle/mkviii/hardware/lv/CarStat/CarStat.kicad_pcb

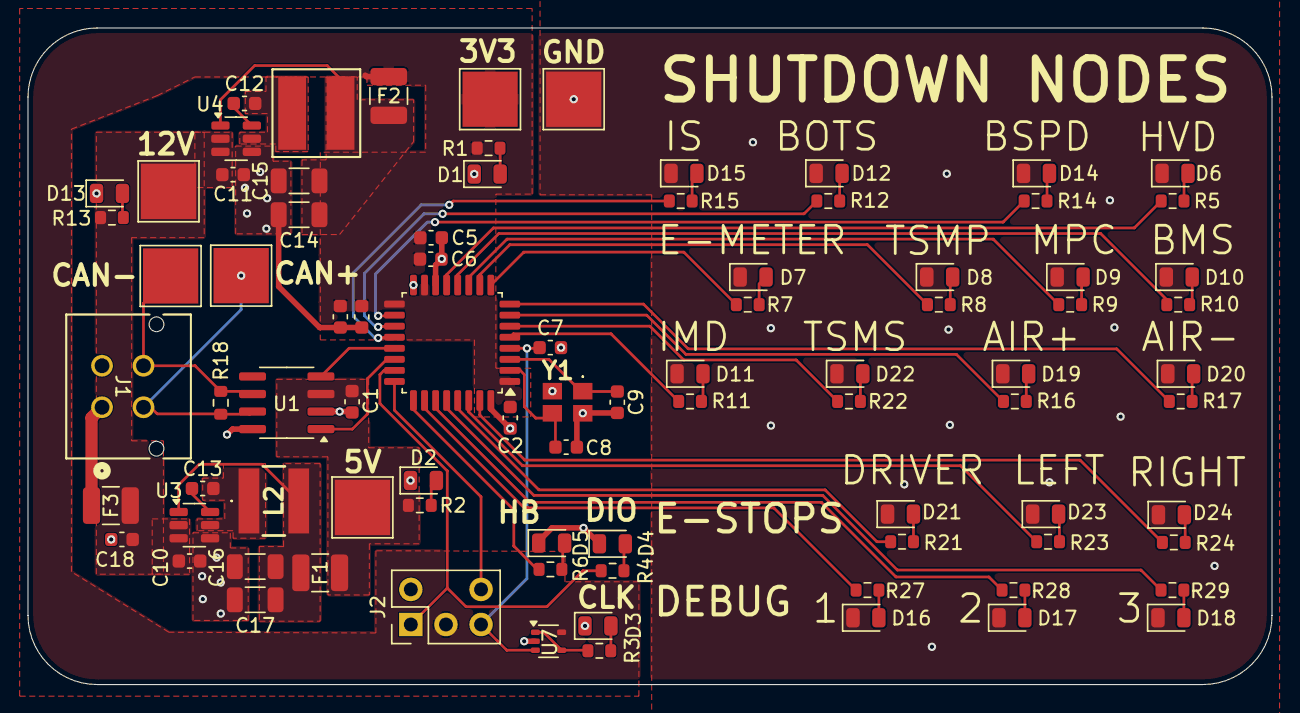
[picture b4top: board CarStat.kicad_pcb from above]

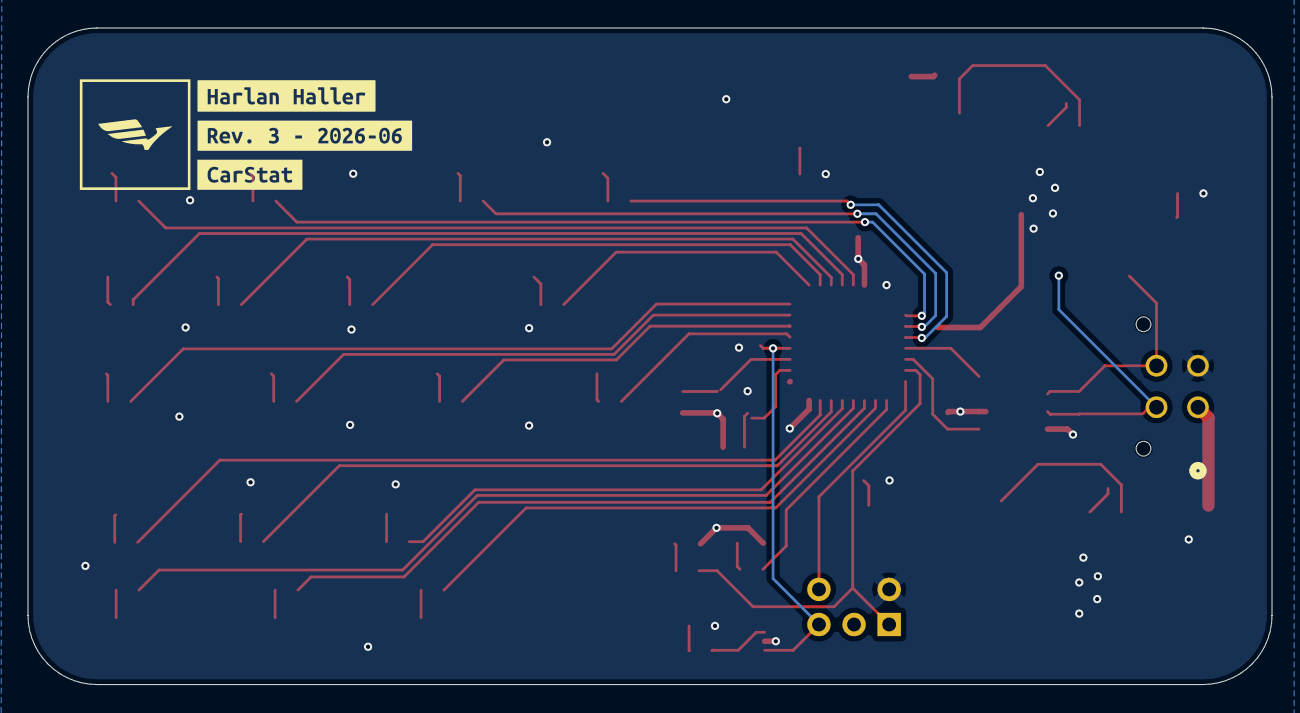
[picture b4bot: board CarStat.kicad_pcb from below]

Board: 2 copper layers, 90.0 x 47.5 mm, 89 parts (3 on the bottom side), 64 nets.

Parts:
C1, C2, C3, C7, C12, C13: C_0.1uF_16V; C_0603_1608Metric
C4: C_4.7uF_25V; C_0603_1608Metric
C5: C_1uF_25V; C_0603_1608Metric
C6: C_10nF_50V; C_0603_1608Metric
C8, C9: C_30pF_50V; C_0603_1608Metric
C10, C11, C18: C_10uF_35V; C_0603_1608Metric
C14, C15, C16, C17: C_22uF_25V; C_1206_3216Metric
D1, D2, D13: LED; D_0805_2012Metric
D3, D4, D6, D7, D8, D9, D10, D11, D12, D14, D15, D19, D20, D22: D_Green_LED; D_0805_2012Metric
D5, D21, D23, D24: D_Red_LED; D_0805_2012Metric
D16, D17, D18: D_Blue_LED; D_0805_2012Metric
F1, F2, F3: F_500mA_16V; Fuse_1210_3225Metric
J1: 430450412; CONN_SD-43045-005_04_MOL
J2: J_Programming_Pin_Header; J_Programming_Pin_Header_Keyed
L1: L_3.9uH_2A; IND_BOURNS_SRR5018 (L_3.9uH_2A_55m_SMD)
L2: L_4.7uH_2.4A; SRN5020TA4R7M
R1, R2, R3, R4, R5, R6, R7, R8, R9, R10, R11, R12, R13, R14, R15, R16, R17, R21, R22, R23, R24, R27, R28, R29: R_1k_0.1W; R_0603_1608Metric
R18: R_120; R_0603_1608Metric
TP1, TP2, TP3, TP4, TP5, TP6: TestPoint; TestPoint_Pad_4.0x4.0mm
U1: MCP2561-E_SN; SOIC-8_3.9x4.9mm_P1.27mm
U2: STM32G441KBT6; LQFP-32_7x7mm_P0.8mm
U3: AD62305WU-7; SOT-23-6
U4: AP63203WU-7; SOT-23-6
U7: MCP6001T-I/LT; SOT-353_SC-70-5
Y1: X_16MHz_18pF; FA238160000MBC0 (X_16MHz_18pF_SMD - FA-238_16.0000MB-C0)
kibuzzard-6A3E9A3A: G***; kibuzzard-6A3E9A3A
kibuzzard-6A3E9A3F: G***; kibuzzard-6A3E9A3F
kibuzzard-6A3E9B69: G***; kibuzzard-6A3E9B69

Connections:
+3V3: C2.1, C3.1, C4.1, C5.1, C6.1, F2.2, J2.3, R1.1, TP2.1 (1_1), U2.1 (VDD), U2.15 (VDDA), U2.17 (VDD), U7.5 (V+)
+5V: C1.1, F1.2, R2.1, TP3.1 (1_1), U1.3 (VDD)
+12V: C10.1, C11.1, C18.1, F3.2, R13.1, TP4.1 (1_1), U3.2 (EN), U3.3 (VIN), U4.2 (EN), U4.3 (VIN)
/+12VIN: F3.1, J1.1
/CAN+: J1.3, R18.1, TP5.1 (1_1), U1.7 (CANH)
/CAN-: J1.4, R18.2, TP6.1 (1_1), U1.6 (CANL)
/CAN_RX: U1.4 (RXD), U2.21 ((FDCAN1_RX/GPIO_EXTI11)PA11)
/CAN_TX: U1.1 (TXD), U2.22 ((FDCAN1_TX/GPIO_EXTI12)PA12)
/Debug1: R27.1, U2.26 ((TIM3_ETR/SPI1_SCK/TIM4_ETR/TIM2_CH2/GP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)
/Debug2: R28.1, U2.27 ((TIM17_BKIN/SPI1_MISO/TIM3_CH1/TIM16_CH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)
/Debug3: R29.1, U2.28 ((TIM17_CH1/SPI1_MOSI/TIM3_CH2/TIM16_BKI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)
/ESTOP.DRIVER: R21.1, U2.29 ((TIM4_CH1/TIM16_CH1N/GPIO_EXTI6)PB6)
/ESTOP.LEFT: R23.1, U2.30 ((TIM3_CH4/TIM4_CH2/TIM17_CH1N/GPIO_EXTI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)
/ESTOP.RIGHT: R24.1, U2.31 ((TIM4_CH3/TIM16_CH1/GPIO_EXTI8)PB8-BOOT0)
/HEARTBEAT: R6.1, U2.25 ((TIM2_ETR/TIM2_CH1/GPIO_EXTI15)PA15)
/NRST: C7.1, J2.4, U2.4 ((GPIO_EXTI10)PG10-NRST), U7.3 (+)
/SHDN.AIR-N: R17.1, U2.8 ((TIM15_CH2/USART2_RX/TIM2_CH4/GPIO_EXTI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)
/SHDN.AIR-P: R16.1, U2.7 ((TIM15_CH1/USART2_TX/TIM2_CH3/GPIO_EXTI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)
/SHDN.BMS: R10.1, U2.12 ((TIM3_CH2/TIM17_CH1/GPIO_EXTI7/ADC2_IN4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)
/SHDN.BOTS: R12.1, U2.19 ((TIM2_CH3/TIM15_BKIN/USART1_TX/GPIO_EXT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)
/SHDN.BSPD: R14.1, U2.18 ((TIM4_ETR/USART1_CK/GPIO_EXTI8)PA8)
/SHDN.EMETER: R7.1, U2.9 ((USART2_CK/TIM3_CH2/GPIO_EXTI4/ADC2_IN1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)
/SHDN.HVD: R5.1, U2.13 ((TIM3_CH3/GPIO_EXTI0/ADC1_IN15)PB0*)
/SHDN.IMD: R11.1, U2.5 ((TIM2_ETR/TIM2_CH1/GPIO_EXTI0/ADC2_IN1/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)
/SHDN.IS: R15.1, U2.20 ((TIM2_CH4/USART1_RX/TIM17_BKIN/GPIO_EXT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)
/SHDN.MPC: R9.1, U2.11 ((TIM3_CH1/TIM16_CH1/GPIO_EXTI6/ADC2_IN3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)
/SHDN.TSMP: R8.1, U2.10 ((TIM2_ETR/TIM2_CH1/GPIO_EXTI5/ADC2_IN13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)
/SHDN.TSMS: R22.1, U2.6 ((TIM15_CH1N/TIM2_CH2/GPIO_EXTI1/ADC2_IN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)
/SWCLK: J2.5, U2.24 ((SYS_JTCK-SWCLK/GPIO_EXTI14)PA14)
/SWDIO: J2.1, R4.1, U2.23 ((SYS_JTMS-SWDIO/GPIO_EXTI13)PA13)
GND: C1.2, C2.2, C3.2, C4.2, C5.2, C6.2, C7.2, C8.2, C9.1, C10.2, C11.2, C14.2, C15.2, C16.2, C17.2, C18.2, D1.1 (K), D2.1 (K), D3.1 (K), D4.1 (K), D5.1 (K), D6.1 (K), D7.1 (K), D8.1 (K), D9.1 (K), D10.1 (K), D11.1 (K), D12.1 (K), D13.1 (K), D14.1 (K), D15.1 (K), D16.1 (K), D17.1 (K), D18.1 (K), D19.1 (K), D20.1 (K), D21.1 (K), D22.1 (K), D23.1 (K), D24.1 (K), J1.2, J2.2, TP1.1 (1_1), U1.2 (VSS), U1.8 (STBY), U2.14 (VSSA), U2.16 (VSS), U2.32 (VSS), U3.4 (GND), U4.4 (GND), U7.2 (V-), Y1.2, Y1.4
unnamed: D1.2 (A), R1.2
unnamed: D2.2 (A), R2.2
unnamed: D3.2 (A), R3.2
unnamed: D4.2 (A), R4.2
unnamed: D5.2 (A), R6.2
unnamed: D6.2 (A), R5.2
unnamed: D7.2 (A), R7.2
unnamed: D8.2 (A), R8.2
unnamed: D9.2 (A), R9.2
unnamed: D10.2 (A), R10.2
unnamed: D11.2 (A), R11.2
unnamed: D12.2 (A), R12.2
unnamed: D13.2 (A), R13.2
unnamed: D14.2 (A), R14.2
unnamed: D15.2 (A), R15.2
unnamed: D16.2 (A), R27.2
unnamed: D17.2 (A), R28.2
unnamed: D18.2 (A), R29.2
unnamed: D19.2 (A), R16.2
unnamed: D20.2 (A), R17.2
unnamed: D21.2 (A), R21.2
unnamed: D22.2 (A), R22.2
unnamed: D23.2 (A), R23.2
unnamed: D24.2 (A), R24.2
unnamed: C8.1, U2.2 (PF0-OSC_IN), Y1.3
unnamed: C9.2, U2.3 (PF1-OSC_OUT), Y1.1
unnamed: C13.1, U3.6 (BST)
unnamed: C16.1, C17.1, F1.1, L2.2, U3.1 (FB)
unnamed: C13.2, L2.1, U3.5 (SW)
unnamed: C12.1, U4.6 (BST)
unnamed: C14.1, C15.1, F2.1, L1.2, U4.1 (FB)
unnamed: C12.2, L1.1, U4.5 (SW)
unnamed: R3.1, U7.1, U7.4 (-)
